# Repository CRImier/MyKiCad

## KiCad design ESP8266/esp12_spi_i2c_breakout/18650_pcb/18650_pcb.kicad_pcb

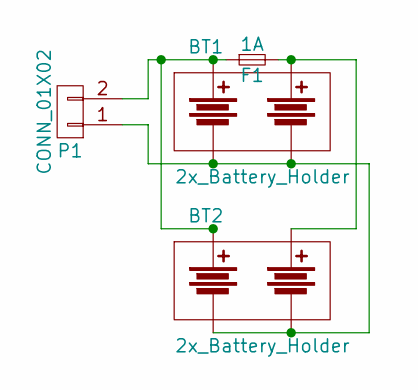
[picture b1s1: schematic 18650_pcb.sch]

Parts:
BT1: 2x_Battery_Holder; KEYSTONE_1048
BT2: 2x_Battery_Holder; BLM_18650_PC4
F1: 1A; Fuse_0679H
P1: CONN_01X02; TerminalBlock_Pheonix_PT-3.5mm_2pol

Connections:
unnamed: BT1.1, BT2.1, F1.1, P1.2
unnamed: BT1.2, BT2.2, F1.2
unnamed: BT1.3, BT1.4, BT2.3, BT2.4, P1.1

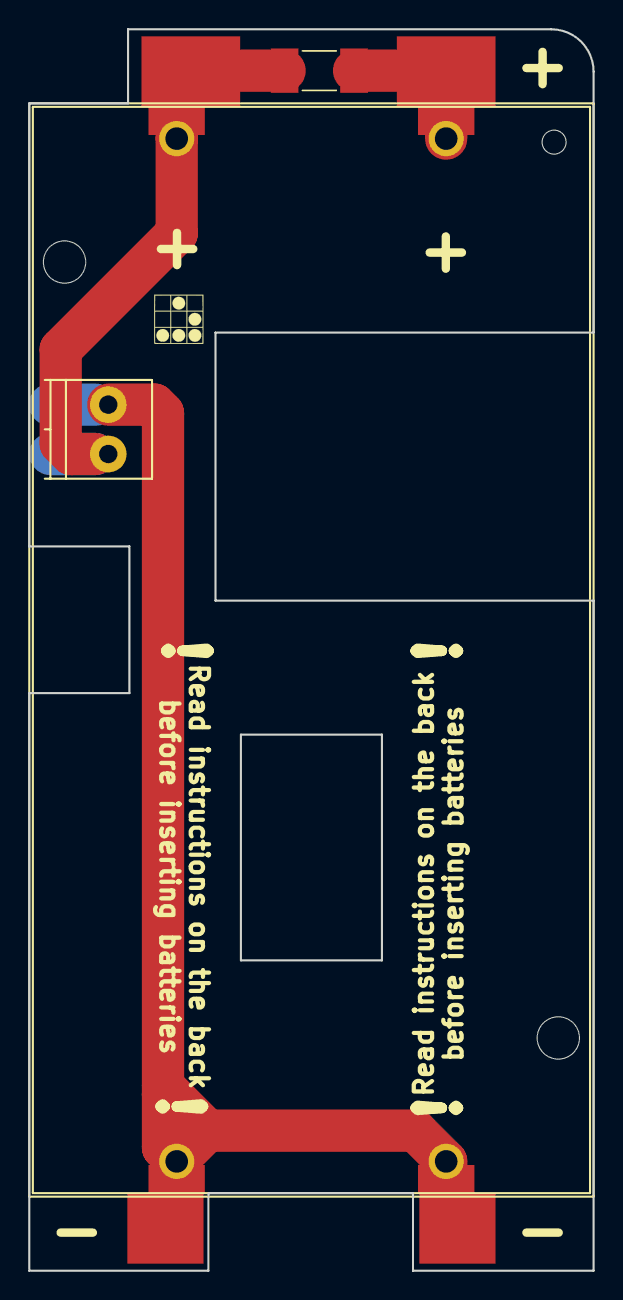
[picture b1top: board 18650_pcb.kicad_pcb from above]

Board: 2 copper layers, 40.0 x 88.0 mm, 4 parts (0 on the bottom side), 3 nets.

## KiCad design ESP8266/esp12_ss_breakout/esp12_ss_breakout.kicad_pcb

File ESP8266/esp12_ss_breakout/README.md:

# SaferSpace ESP12 entry panel controller

This is an entry panel ESP12 controller that can connect to the TTP229 board and the shift registers for LEDs,
as well as has I2C, UART and other connectors for extra devices that can be added.

This board has 5V and 3.3V linear regulators for the base components (ESP,595,TTP229) and also various devices
that could be connected in the future. It also has an RJ45 socket with a configurable pinout that's compatible
with regular passive PoE.

This board has THT cap footprints for regulators, but you can solder SMD caps on the TH pads instead.

Signal names are not silkscreened on the board, since I was ordering it in a rush.

- Version: 1
- PCB size: w*h
- Layer count: 2

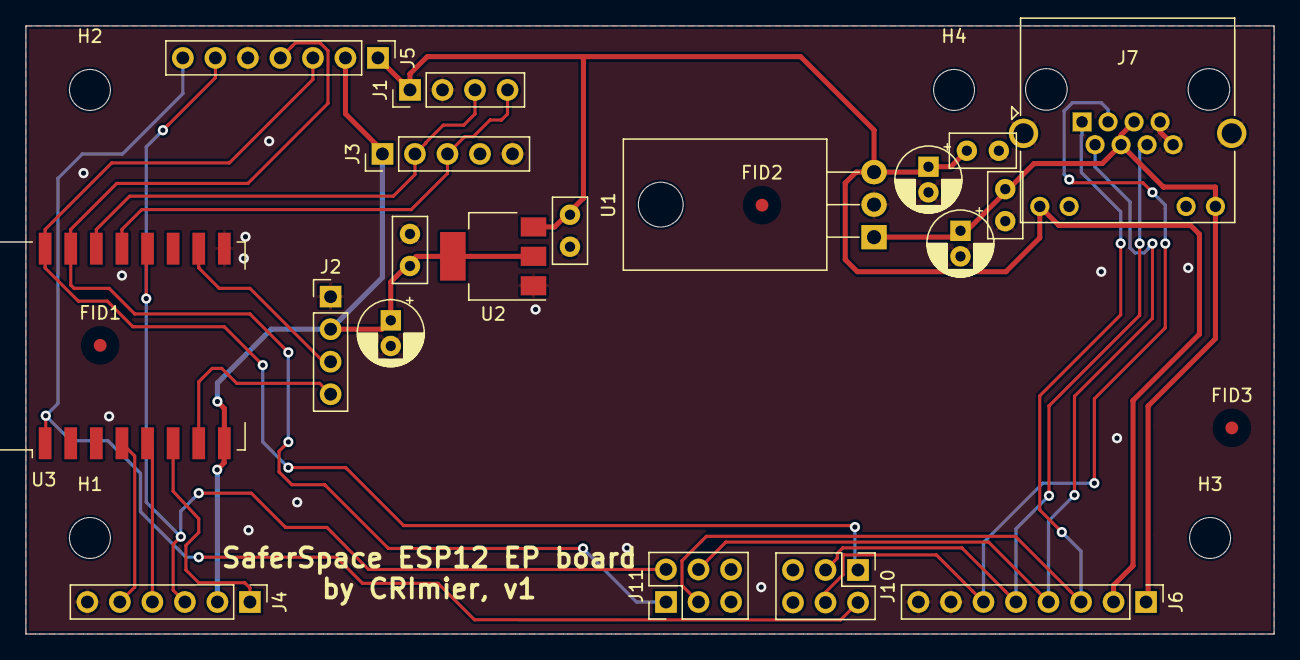
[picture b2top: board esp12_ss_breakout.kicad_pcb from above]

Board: 2 copper layers, 97.5 x 47.5 mm, 26 parts (0 on the bottom side), 19 nets.

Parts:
C4, C5, C6, C7: 100nF; C_Disc_D5.0mm_W2.5mm_P2.50mm
C10, C11, C12: 10uF; CP_Radial_D5.0mm_P2.00mm
FID1, FID2, FID3: Fiducial; Fiducial_1mm_Mask3mm
H1, H2, H3, H4: MountingHole; MountingHole_3.2mm_M3
J1: LCD; PinHeader_1x04_P2.54mm_Vertical
J2: KP; PinHeader_1x04_P2.54mm_Vertical
J3: I2C_RPI; PinHeader_1x05_P2.54mm_Vertical
J4: SHIFT; PinHeader_1x06_P2.54mm_Vertical
J5: PROG; PinHeader_1x07_P2.54mm_Vertical
J6: COMM; PinHeader_1x08_P2.54mm_Vertical
J7: COMM_RJ; RJ45_Amphenol_RJHSE538X
J10: 485_or_STR_TX; PinHeader_2x03_P2.54mm_Vertical
J11: 485_or_STR_RX; PinHeader_2x03_P2.54mm_Vertical
U1: L7805; TO-220-3_Horizontal_TabDown
U2: AP1117-33; SOT-223-3_TabPin2
U3: ESP-12E

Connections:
+3V3: C5.1, C12.1, J2.2, J3.1, J4.2, J5.2, U2.2, U3.8
+5V: C4.1, C7.1, C10.1, J1.1, J5.1, J6.2, J7.9, U1.3, U2.3
+VDC: C6.1, C11.1, J6.1, J7.4, J7.5, J7.12, U1.1
GND: C4.2, C5.2, C6.2, C7.2, C10.2, C11.2, C12.2, J1.2, J2.1, J3.5, J4.6, J5.5, J6.7, J6.8, J7.7, J7.8, J7.SH, U1.2, U2.1, U3.15
I2C_SCL: J1.4, J3.3, U3.19
I2C_SDA: J1.3, J3.2, U3.20
K_SCL: J2.4, U3.7
K_SDO: J2.3, U3.16
R1: J6.3, J7.1, J11.3
R2: J6.4, J7.2, J11.4
RST: J5.7, J10.2, U3.1
RX: J5.4, J11.1, U3.21
S_CLK: J4.4, U3.5
S_DAT: J4.3, J5.6, J11.2, U3.18
S_LAT: J4.5, U3.4
S_PWM: J4.1, U3.6
T1: J6.5, J7.6, J10.3
T2: J6.6, J7.3, J10.4
TX: J5.3, J10.1, U3.22

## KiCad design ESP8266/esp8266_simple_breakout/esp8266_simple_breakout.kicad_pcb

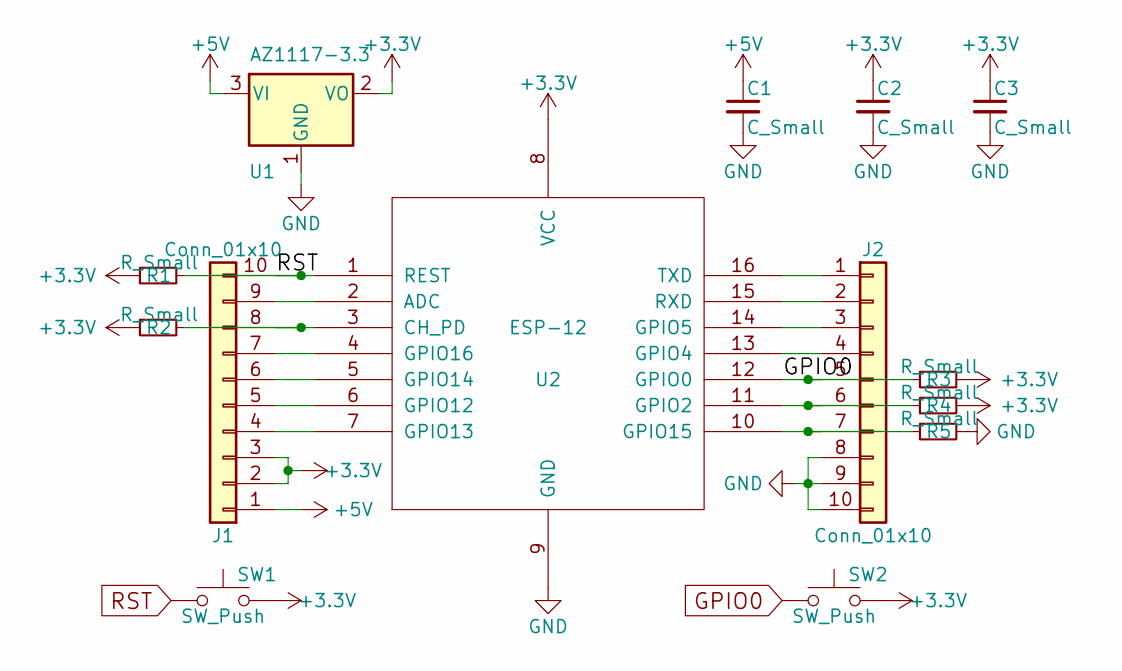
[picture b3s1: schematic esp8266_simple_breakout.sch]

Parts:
C1, C2, C3: C_Small; C_0805
J1, J2: Conn_01x10; Pin_Header_Straight_1x10_Pitch2.54mm
R1, R2, R3, R4, R5: R_Small; R_0603_HandSoldering
SW1, SW2: SW_Push; SW_SPST_EVQPE1
U1: AZ1117-3.3; SOT-223-3Lead_TabPin2
U2: ESP-12

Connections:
+3V3: C2.1, C3.1, J1.2, J1.3, R1.2, R2.2, R3.1, R4.1, SW1.2, SW2.2, U1.2 (VO), U2.8 (VCC)
+5V: C1.1, J1.1, U1.3 (VI)
GND: C1.2, C2.2, C3.2, J2.8, J2.9, J2.10, R5.1, U1.1 (GND), U2.9 (GND)
GPIO0: J2.5, R3.2, SW2.1, U2.12 (GPIO0)
unnamed: J1.4, U2.7 (GPIO13)
unnamed: J1.5, U2.6 (GPIO12)
unnamed: J1.6, U2.5 (GPIO14)
unnamed: J1.7, U2.4 (GPIO16)
unnamed: J1.8, R2.1, U2.3 (CH_PD)
unnamed: J1.9, U2.2 (ADC)
unnamed: J2.1, U2.16 (TXD)
unnamed: J2.2, U2.15 (RXD)
unnamed: J2.3, U2.14 (GPIO5)
unnamed: J2.4, U2.13 (GPIO4)
unnamed: J2.6, R4.2, U2.11 (GPIO2)
unnamed: J2.7, R5.2, U2.10 (GPIO15)
RST: J1.10, R1.1, SW1.1, U2.1 (REST)

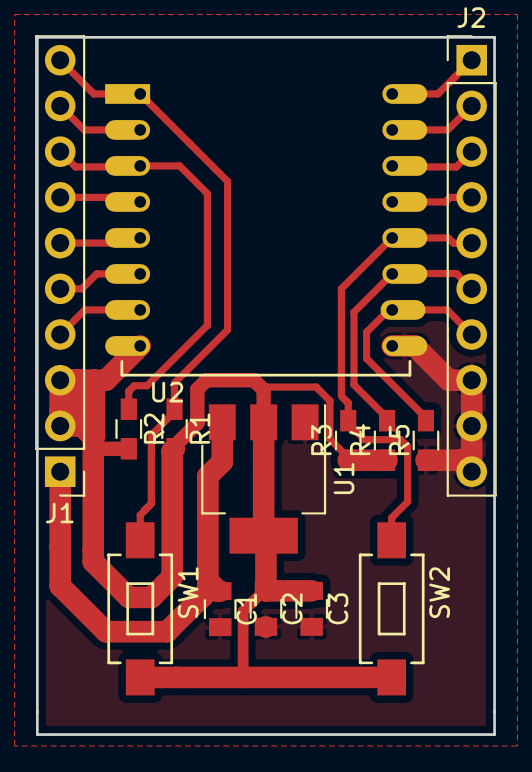
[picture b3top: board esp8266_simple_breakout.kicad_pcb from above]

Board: 2 copper layers, 25.4 x 38.7 mm, 14 parts (0 on the bottom side), 17 nets.

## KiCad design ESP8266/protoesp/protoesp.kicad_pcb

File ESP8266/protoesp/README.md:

# ProtoESP 8266

- [Main repo is here.](https://github.com/CRImier/ProtoESP/)
- [Project file releases are available here.](https://github.com/CRImier/ProtoESP/releases)
- [Board release thread on Twitter](https://twitter.com/CRImierTech/status/1481676889353773059)
- [Start of original Twitter thread chain, describing design intentions and process](https://twitter.com/CRImierTech/status/1473325419478847494)

Signal names are silkscreened on the board's bottom layers.

- Software: Kicad 7
- Version: ^__^
- PCB size: 97.5mmx90mm
- Layer count: 2

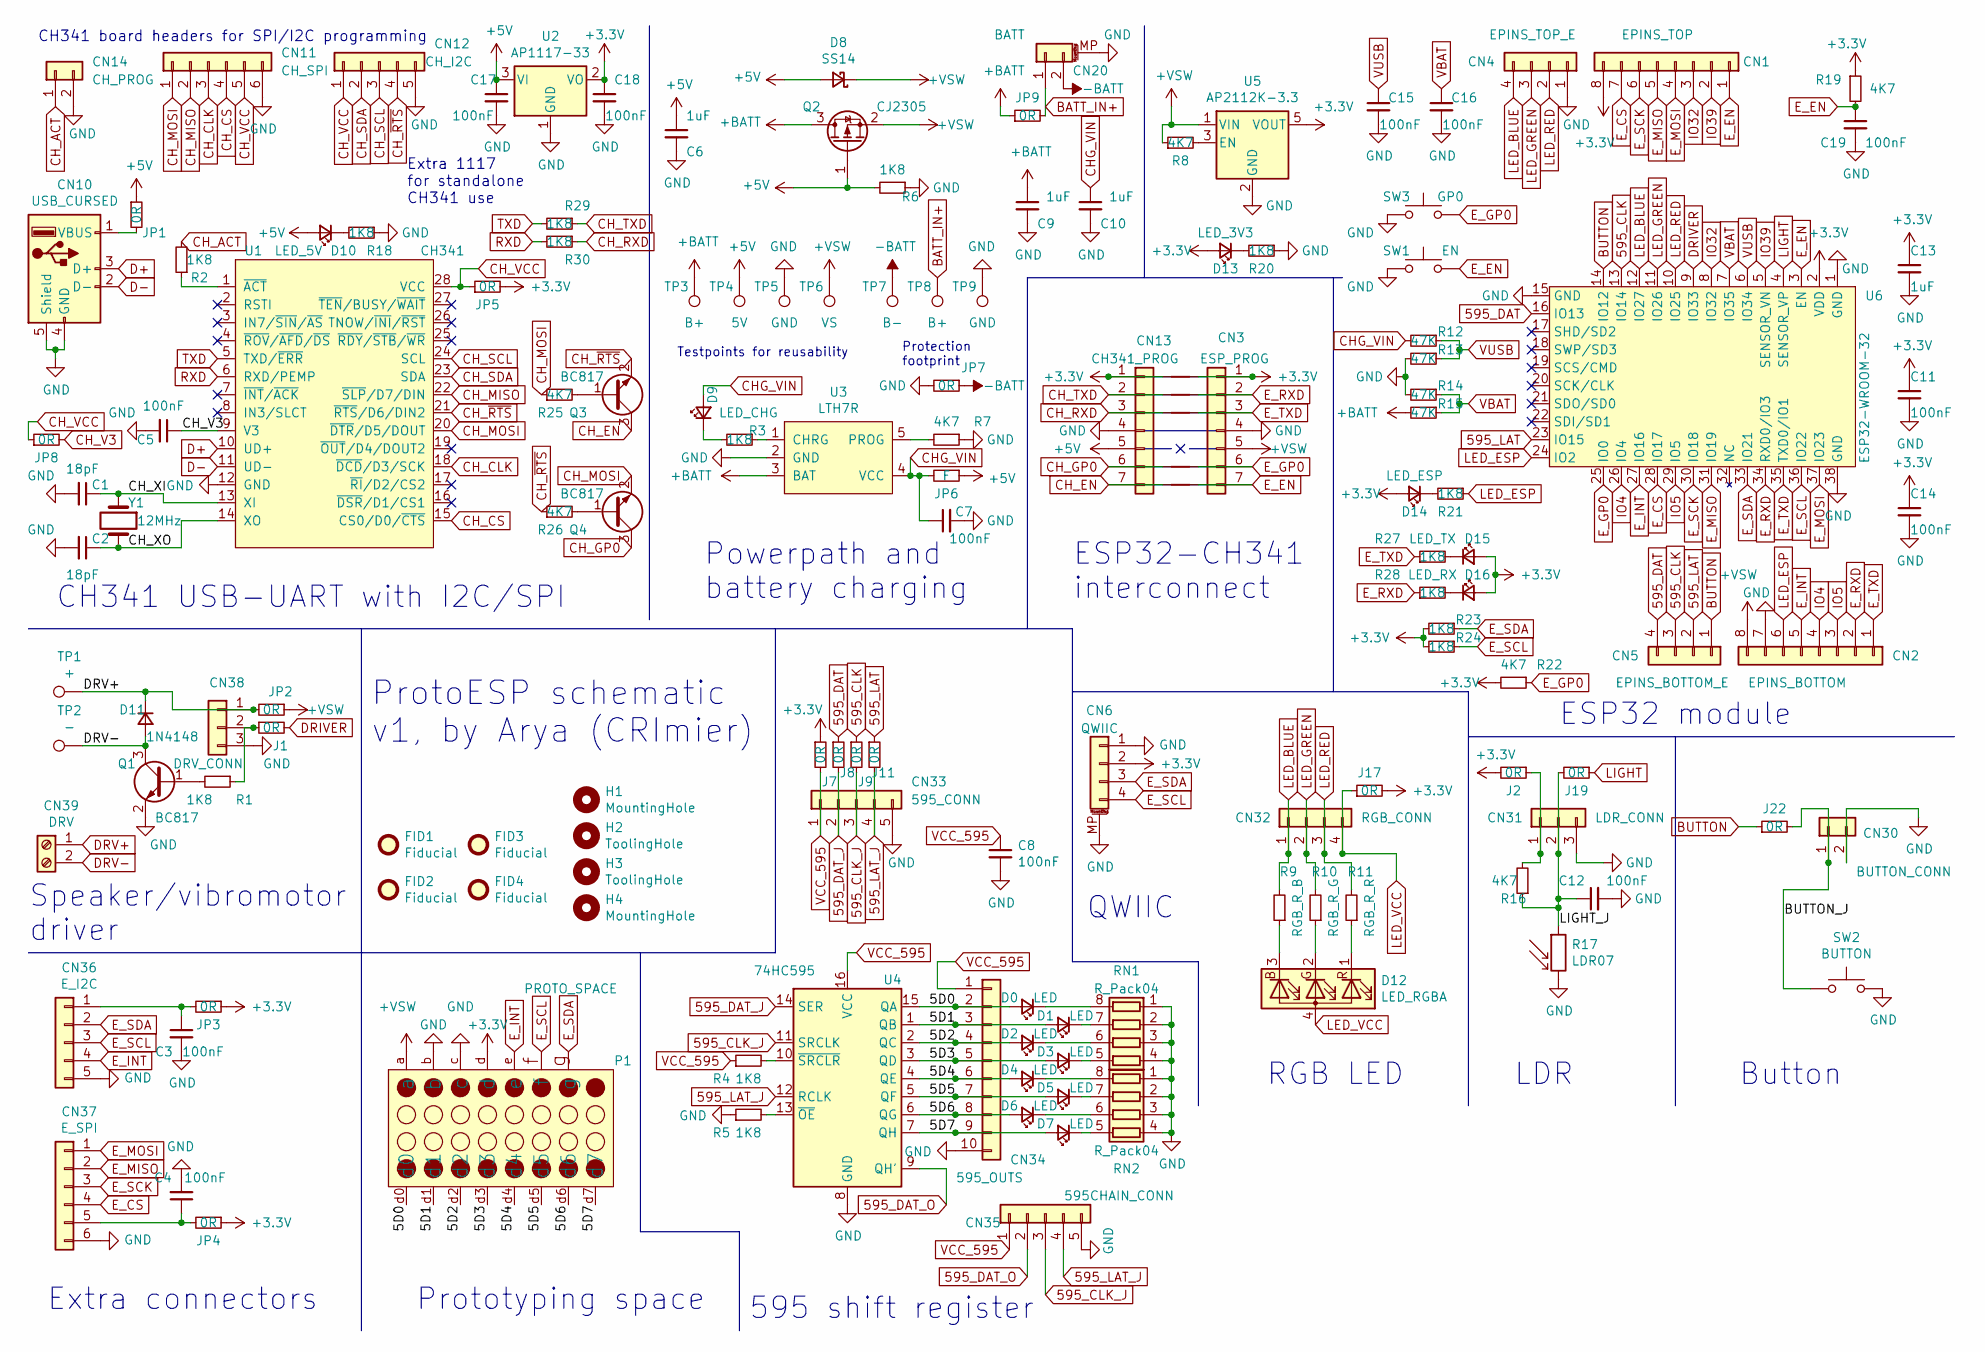
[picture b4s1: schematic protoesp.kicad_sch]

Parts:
C1, C2: 18pF; C_0603_1608Metric
C3, C4, C5, C7, C8, C11, C12, C14, C15, C16, C17, C18, C19: 100nF; C_0805_2012Metric
C6, C9, C10, C13: 1uF; C_0805_2012Metric
CN1: EPINS_TOP; PinHeader_1x08_P2.54mm_Vertical
CN2: EPINS_BOTTOM; PinHeader_1x08_P2.54mm_Vertical
CN3: ESP_PROG; PinHeader_1x07_P2.54mm_Vertical
CN4: EPINS_TOP_E; PinHeader_1x04_P2.54mm_Vertical
CN5: EPINS_BOTTOM_E; PinHeader_1x04_P2.54mm_Vertical
CN6: QWIIC; JST_SH_BM04B-SRSS-TB_1x04-1MP_P1.00mm_Vertical
CN10: USB_CURSED; USB_Combined
CN11: CH_SPI; PinSocket_1x06_P2.54mm_Horizontal
CN12: CH_I2C; PinSocket_1x05_P2.54mm_Horizontal
CN13: CH341_PROG; PinHeader_1x07_P2.54mm_Vertical
CN14: CH_PROG; PinSocket_1x02_P2.54mm_Vertical
CN20: BATT; JST_PH_S2B-PH-SM4-TB_02x2.00mm_Angled
CN30: BUTTON_CONN; PinHeader_1x02_P2.54mm_Vertical
CN31: LDR_CONN; PinHeader_1x03_P2.54mm_Vertical
CN32: RGB_CONN; PinHeader_1x04_P2.54mm_Vertical
CN33: 595_CONN; PinHeader_1x05_P2.54mm_Vertical
CN34: 595_OUTS; PinSocket_1x10_P2.54mm_Vertical
CN35: 595CHAIN_CONN; PinHeader_1x05_P2.54mm_Vertical
CN36: E_I2C; PinSocket_1x05_P2.54mm_Horizontal
CN37: E_SPI; PinSocket_1x06_P2.54mm_Horizontal
CN38: DRV_CONN; PinHeader_1x03_P2.54mm_Vertical
CN39: DRV; TerminalBlock_bornier-2_P5.08mm
D0, D1, D2, D3, D4, D5, D6, D7: LED; LED_0805_2012Metric
D8: SS14; D_SMA
D9: LED_CHG; LED_0805_2012Metric
D10: LED_5V; LED_0805_2012Metric
D11: 1N4148; D_SOD-123
D12: LED_RGBA; LED_RGB_1210
D13: LED_3V3; LED_0805_2012Metric
D14: LED_ESP; LED_0805_2012Metric
D15: LED_TX; LED_0805_2012Metric
D16: LED_RX; LED_0805_2012Metric
FID1, FID2, FID3, FID4: Fiducial; Fiducial_1mm_Mask2mm
H1, H4: MountingHole; JLCPCBToolingHole
H2, H3: ToolingHole; JLCPCBToolingHole
J1, J2, J7, J8, J9, J11, J17, J19, J22: 0R; R_0603_1608Metric
JP1, JP2, JP3, JP4, JP5, JP7, JP8, JP9: 0R; R_0805_2012Metric
JP6: F; R_0805_2012Metric
NT1, NT2, NT3, NT6, NT7: Net-Tie_2; NetTie-2_SMD_Pad0.5mm
P1: PROTO_SPACE; PROTO_THT_SMD_FULL
Q1, Q3, Q4: BC817; SOT-23
Q2: CJ2305; SOT-23
R1, R2, R3, R4, R5, R6, R18, R20, R21, R23, R24, R27, R28, R29, R30: 1K8; R_0603_1608Metric
R7, R8, R16, R19, R22, R25, R26: 4K7; R_0603_1608Metric
R9: RGB_R_B; R_0603_1608Metric
R10: RGB_R_G; R_0603_1608Metric
R11: RGB_R_R; R_0603_1608Metric
R12, R13, R14, R15: 47K; R_0603_1608Metric
R17: LDR07; R_LDR_5.1x4.3mm_P3.4mm_Vertical
RN1, RN2: R_Pack04; R_Array_Concave_4x0603
SW1: EN; SW_SPST_SKQG_WithStem
SW2: BUTTON; SW_SPST_SKQG_WithStem
SW3: GP0; SW_SPST_SKQG_WithStem
TP1: +; TestPoint_Pad_2.0x2.0mm
TP2: -; TestPoint_Pad_2.0x2.0mm
TP3, TP8: B+; TestPoint_Pad_2.0x2.0mm
TP4: 5V; TestPoint_Pad_2.0x2.0mm
TP5, TP9: GND; TestPoint_Pad_2.0x2.0mm
TP6: VS; TestPoint_Pad_2.0x2.0mm
TP7: B-; TestPoint_Pad_2.0x2.0mm
U1: CH341; SOIC-28W_SOIC16_CH34x_Combined
U2: AP1117-33; SOT-223-3_TabPin2
U3: LTH7R; SOT-23-5
U4: 74HC595; SOP-16_4.55x10.3mm_P1.27mm
U5: AP2112K-3.3; SOT-23-5
U6: ESP32-WROOM-32
Y1: 12MHz; Crystal_HC49-U_Vertical

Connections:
595_CLK: CN5.3, J9.1, U6.13 (IO14)
595_CLK_J: CN33.3, CN35.3, J9.2, U4.11 (SRCLK)
595_DAT: CN5.4, J8.1, U6.16 (IO13)
595_DAT_J: CN33.2, J8.2, U4.14 (SER)
595_DAT_O: CN35.2, U4.9 (QH')
595_LAT: CN5.2, J11.1, U6.23 (IO15)
595_LAT_J: CN33.4, CN35.4, J11.2, U4.12 (RCLK)
+3V3: C11.1, C13.1, C14.1, C18.1, CN1.8, CN3.1, CN6.2, CN13.1, D13.2 (A), D14.2 (A), D15.2 (A), D16.2 (A), J2.2, J7.1, J17.2, JP3.1, JP4.1, JP5.2, NT1.1, NT1.2, P1.d, R19.1, R22.2, R23.2, R24.2, U2.2 (VO), U5.5 (VOUT), U6.2 (VDD)
+5V: C6.1, C17.1, CN13.5, D8.2 (A), D10.2 (A), JP1.1, JP6.1, Q2.1 (G), R6.2, TP4.1, U2.3 (VI)
+BATT: C9.1, JP9.1, Q2.3 (D), R15.2, TP3.1, U3.3 (BAT)
+VSW: CN2.8, CN3.5, D8.1 (K), JP2.1, P1.a, Q2.2 (S), R8.1, TP6.1, U5.1 (VIN)
-BATT: CN20.2, JP7.1, TP7.1
/5D0: CN34.2, D0.2 (A), P1.d0, U4.15 (QA)
/5D1: CN34.3, D1.2 (A), P1.d1, U4.1 (QB)
/5D2: CN34.4, D2.2 (A), P1.d2, U4.2 (QC)
/5D3: CN34.5, D3.2 (A), P1.d3, U4.3 (QD)
/5D4: CN34.6, D4.2 (A), P1.d4, U4.4 (QE)
/5D5: CN34.7, D5.2 (A), P1.d5, U4.5 (QF)
/5D6: CN34.8, D6.2 (A), P1.d6, U4.6 (QG)
/5D7: CN34.9, D7.2 (A), P1.d7, U4.7 (QH)
/BUTTON_J: CN30.1, J22.2, SW2.1
/CH_XI: C1.1, U1.13 (XI), Y1.1
/CH_XO: C2.1, U1.14 (XO), Y1.2
/LIGHT_J: C12.1, CN31.2, J19.2, R16.1, R17.1
BATT_IN+: CN20.1, JP9.2, TP8.1
BUTTON: CN5.1, J22.1, U6.14 (IO12)
CHG_VIN: C7.1, C10.1, D9.2 (A), JP6.2, R12.2, U3.4 (VCC)
CH_ACT: CN14.1, R2.2
CH_CLK: CN11.3, U1.18 (~DCD/D3/SCK)
CH_CS: CN11.4, U1.15 (CS0/D0/~CTS)
CH_EN: CN13.7, NT7.1, Q3.3 (C)
CH_GP0: CN13.6, NT6.1, Q4.3 (C)
CH_MISO: CN11.2, U1.22 (~SLP/D7/DIN)
CH_MOSI: CN11.1, Q4.2 (E), R25.1, U1.20 (~DTR/D5/DOUT)
CH_RXD: CN13.3, NT3.1, R30.1
CH_SCL: CN12.3, U1.24 (SCL)
CH_SDA: CN12.2, U1.23 (SDA)
CH_TXD: CN13.2, NT2.1, R29.1
CH_V3: C5.1, JP8.2, U1.9 (V3)
CH_VCC: CN11.5, CN12.1, JP5.1, JP8.1, U1.28 (VCC)
CH_~RTS: CN12.4, Q3.2 (E), R26.1, U1.21 (~RTS/D6/DIN2)
D+: CN10.3 (D+), U1.10 (UD+)
D-: CN10.2 (D-), U1.11 (UD-)
DRIVER: J1.2, U6.9 (IO33)
DRV+: CN38.1, CN39.1, D11.1 (K), JP2.2, TP1.1
DRV-: CN39.2, D11.2 (A), Q1.3 (C), TP2.1
E_CS: CN1.7, CN37.4, U6.28 (IO17)
E_EN: C19.1, CN1.1, CN3.7, NT7.2, R19.2, SW1.2, U6.3 (EN)
E_GP0: CN3.6, NT6.2, R22.1, SW3.2, U6.25 (IO0)
E_INT: CN2.5, CN36.4, P1.e, U6.27 (IO16)
E_MISO: CN1.5, CN37.2, U6.31 (IO19)
E_MOSI: CN1.4, CN37.1, U6.37 (IO23)
E_RXD: CN2.2, CN3.2, NT2.2, R28.1, U6.34 (RXD0/IO3)
E_SCK: CN1.6, CN37.3, U6.30 (IO18)
E_SCL: CN6.4, CN36.3, P1.f, R24.1, U6.36 (IO22)
E_SDA: CN6.3, CN36.2, P1.g, R23.1, U6.33 (IO21)
E_TXD: CN2.1, CN3.3, NT3.2, R27.1, U6.35 (TXD0/IO1)
GND: C1.2, C2.2, C3.2, C4.2, C5.2, C6.2, C7.2, C8.2, C9.2, C10.2, C11.2, C12.2, C13.2, C14.2, C15.2, C16.2, C17.2, C18.2, C19.2, CN2.7, CN3.4, CN4.1, CN6.1, CN6.MP (MountPin), CN10.4 (GND), CN10.5 (Shield), CN11.6, CN12.5, CN13.4, CN14.2, CN20.MP (MountPin), CN30.2, CN31.3, CN33.5, CN34.10, CN35.5, CN36.5, CN37.6, CN38.3, JP7.2, P1.b, P1.c, Q1.2 (E), R5.1, R6.1, R7.1, R13.2, R14.2, R17.2, R18.1, R20.1, RN1.1 (R1.1), RN1.2 (R2.1), RN1.3 (R3.1), RN1.4 (R4.1), RN2.1 (R1.1), RN2.2 (R2.1), RN2.3 (R3.1), RN2.4 (R4.1), SW1.1, SW2.2, SW3.1, TP5.1, TP9.1, U1.12 (GND), U2.1 (GND), U3.2 (GND), U4.8 (GND), U5.2 (GND), U6.1 (GND), U6.15 (GND), U6.38 (GND), U6.39 (GND)
IO4: CN2.4, U6.26 (IO4)
IO5: CN2.3, U6.29 (IO5)
IO32: CN1.3, U6.8 (IO32)
IO39: CN1.2, U6.5 (SENSOR_VN)
LED_BLUE: CN4.4, CN32.1, R9.2, U6.12 (IO27)
LED_ESP: CN2.6, R21.1, U6.24 (IO2)
LED_GREEN: CN4.3, CN32.2, R10.2, U6.11 (IO26)
LED_RED: CN4.2, CN32.3, R11.2, U6.10 (IO25)
LED_VCC: CN32.4, D12.4 (A), J17.1
LIGHT: J19.1, U6.4 (SENSOR_VP)
unnamed: C3.1, CN36.1, JP3.2
unnamed: C4.1, CN37.5, JP4.2
unnamed: CN10.1 (VBUS), JP1.2
unnamed: CN31.1, J2.1, R16.2
unnamed: CN38.2, J1.1, R1.1
unnamed: D0.1 (K), RN1.8 (R1.2)
unnamed: D1.1 (K), RN1.7 (R2.2)
unnamed: D2.1 (K), RN1.6 (R3.2)
unnamed: D3.1 (K), RN1.5 (R4.2)
unnamed: D4.1 (K), RN2.8 (R1.2)
unnamed: D5.1 (K), RN2.7 (R2.2)
unnamed: D6.1 (K), RN2.6 (R3.2)
unnamed: D7.1 (K), RN2.5 (R4.2)
unnamed: D9.1 (K), R3.2
unnamed: D10.1 (K), R18.2
unnamed: D12.1 (RK), R11.1
unnamed: D12.2 (GK), R10.1
unnamed: D12.3 (BK), R9.1
unnamed: D13.1 (K), R20.2
unnamed: D14.1 (K), R21.2
unnamed: D15.1 (K), R27.2
unnamed: D16.1 (K), R28.2
unnamed: Q1.1 (B), R1.2
unnamed: Q3.1 (B), R25.2
unnamed: Q4.1 (B), R26.2
unnamed: R2.1, U1.1 (~ACT)
unnamed: R3.1, U3.1 (CHRG)
unnamed: R4.2, U4.10 (~SRCLR)
unnamed: R5.2, U4.13 (~OE)
unnamed: R7.2, U3.5 (PROG)
unnamed: R8.2, U5.3 (EN)
RXD: R30.2, U1.6 (RXD/PEMP)
TXD: R29.2, U1.5 (TXD/~ERR)
VBAT: C16.1, R14.1, R15.1, U6.7 (IO35)
VCC_595: C8.1, CN33.1, CN34.1, CN35.1, J7.2, R4.1, U4.16 (VCC)
VUSB: C15.1, R12.1, R13.1, U6.6 (IO34)

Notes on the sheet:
Extra connectors
Protection footprint
Prototyping space
ESP32-CH341 interconnect
ProtoESP schematic v1, by Arya (CRImier)
Testpoints for reusability
CH341 USB-UART with I2C/SPI
Powerpath and battery charging
ESP32 module
595 shift register
Button
Extra 1117 for standalone CH341 use
CH341 board headers for SPI/I2C programming
RGB LED
LDR
QWIIC
Speaker/vibromotor driver

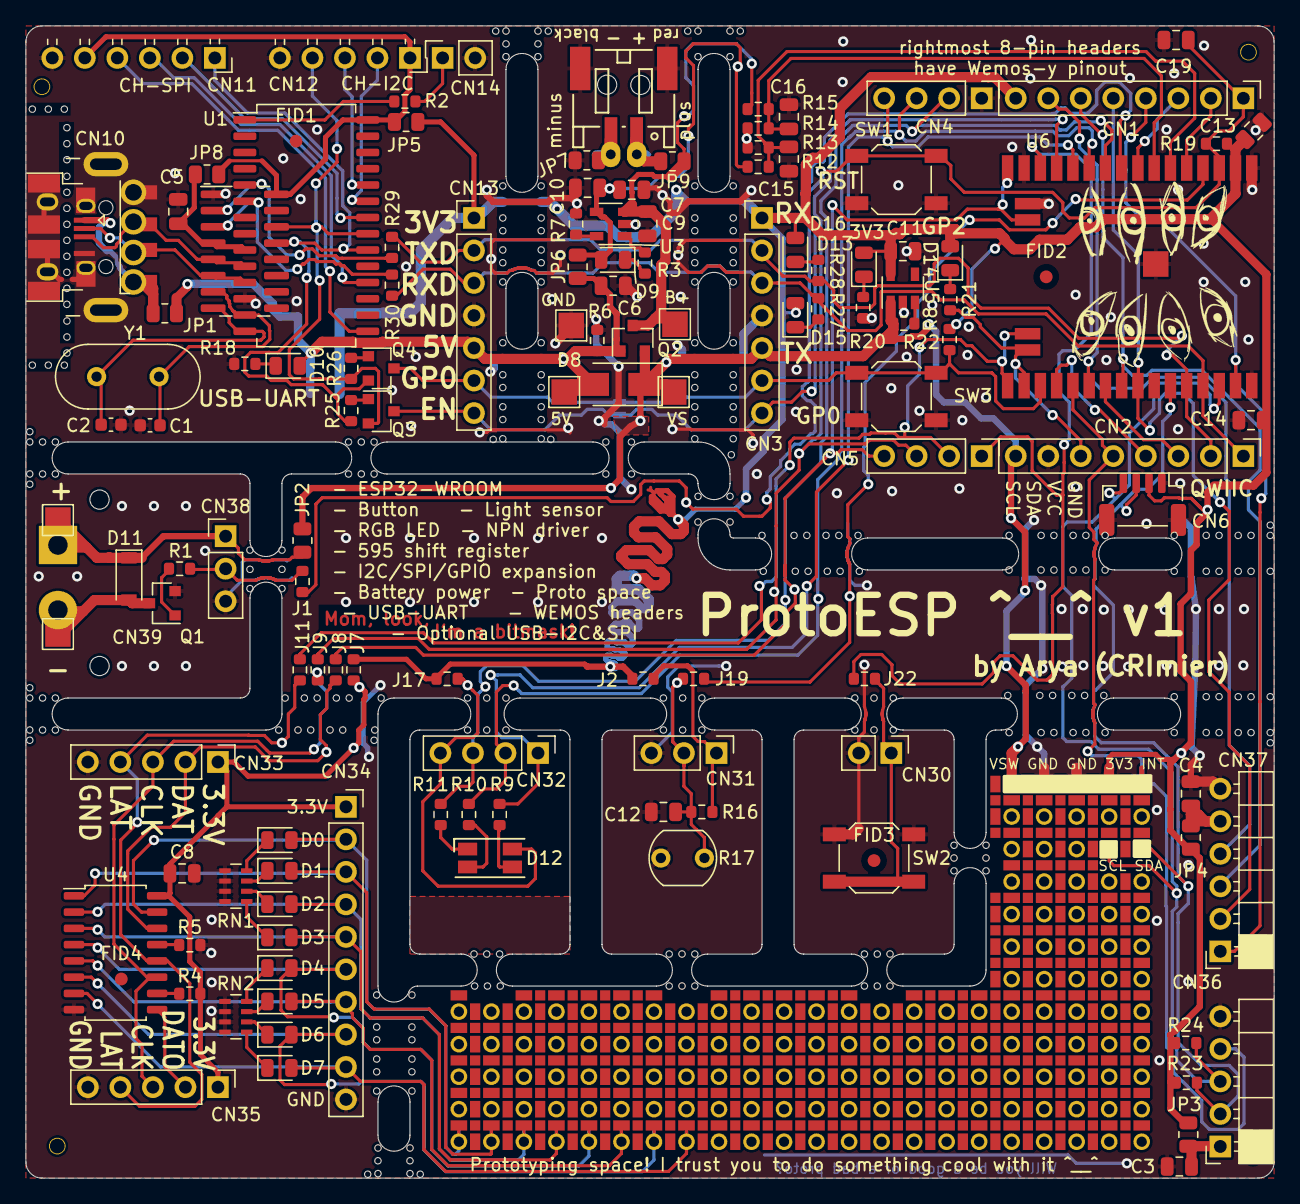
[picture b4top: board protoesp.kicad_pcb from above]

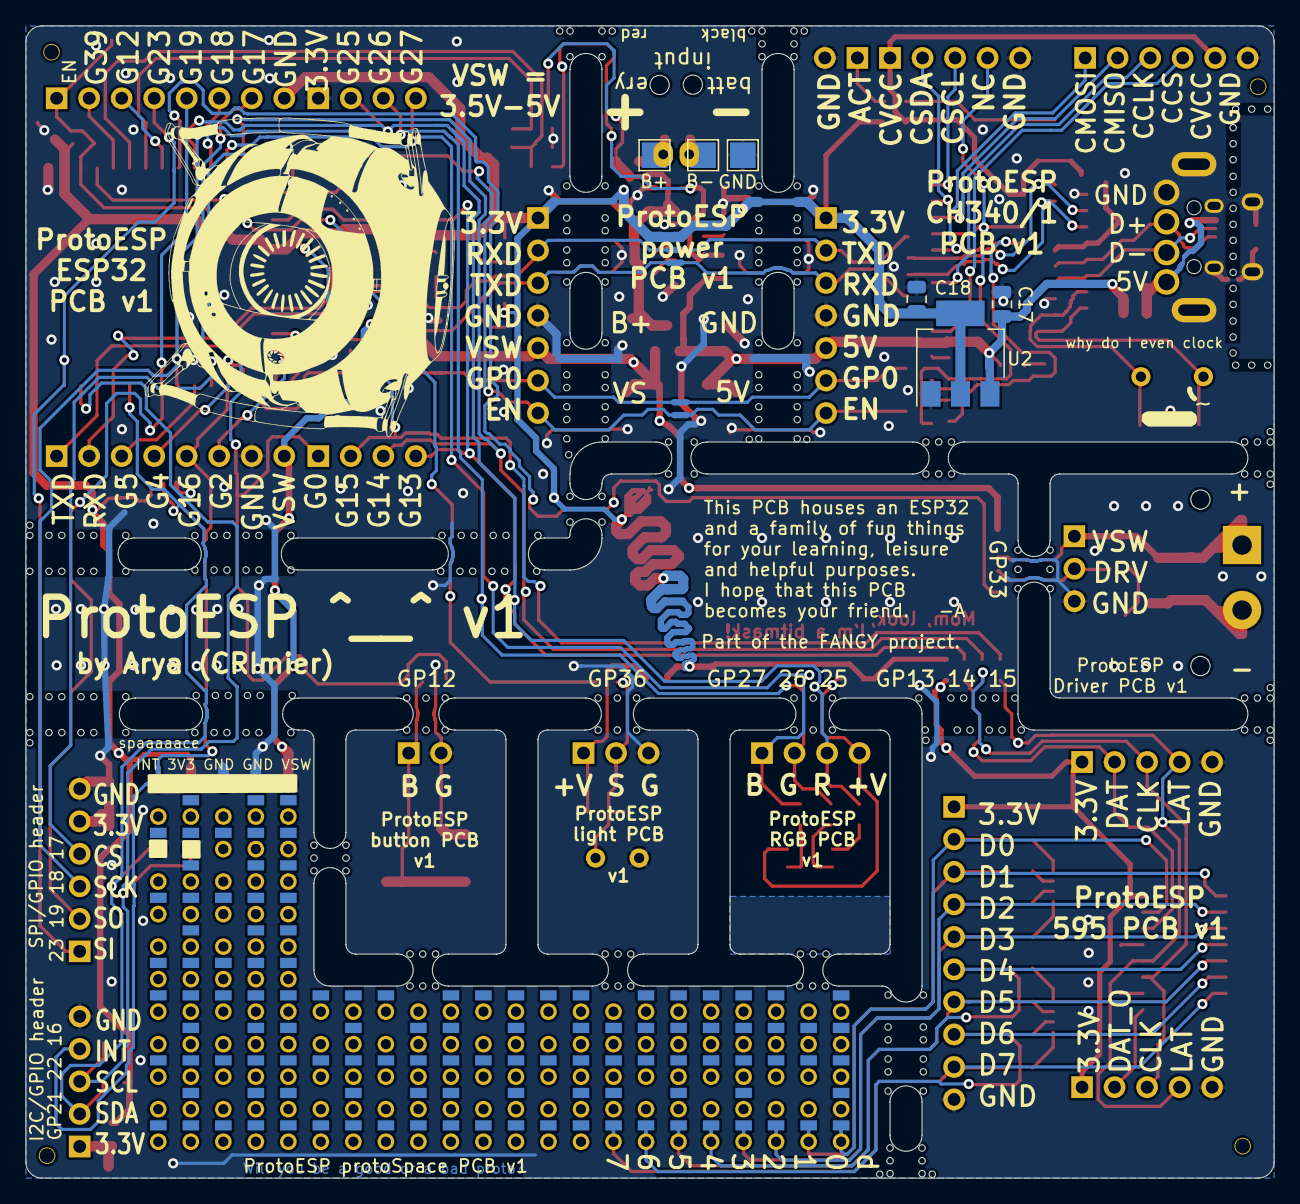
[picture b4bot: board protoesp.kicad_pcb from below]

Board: 2 copper layers, 97.5 x 90.0 mm, 149 parts (11 on the bottom side), 104 nets.

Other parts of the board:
H1#2, H1#3, H1#5: pin_hole; PinHole_1,5mm
H1#4: MountingHole; JLCPCBToolingHole

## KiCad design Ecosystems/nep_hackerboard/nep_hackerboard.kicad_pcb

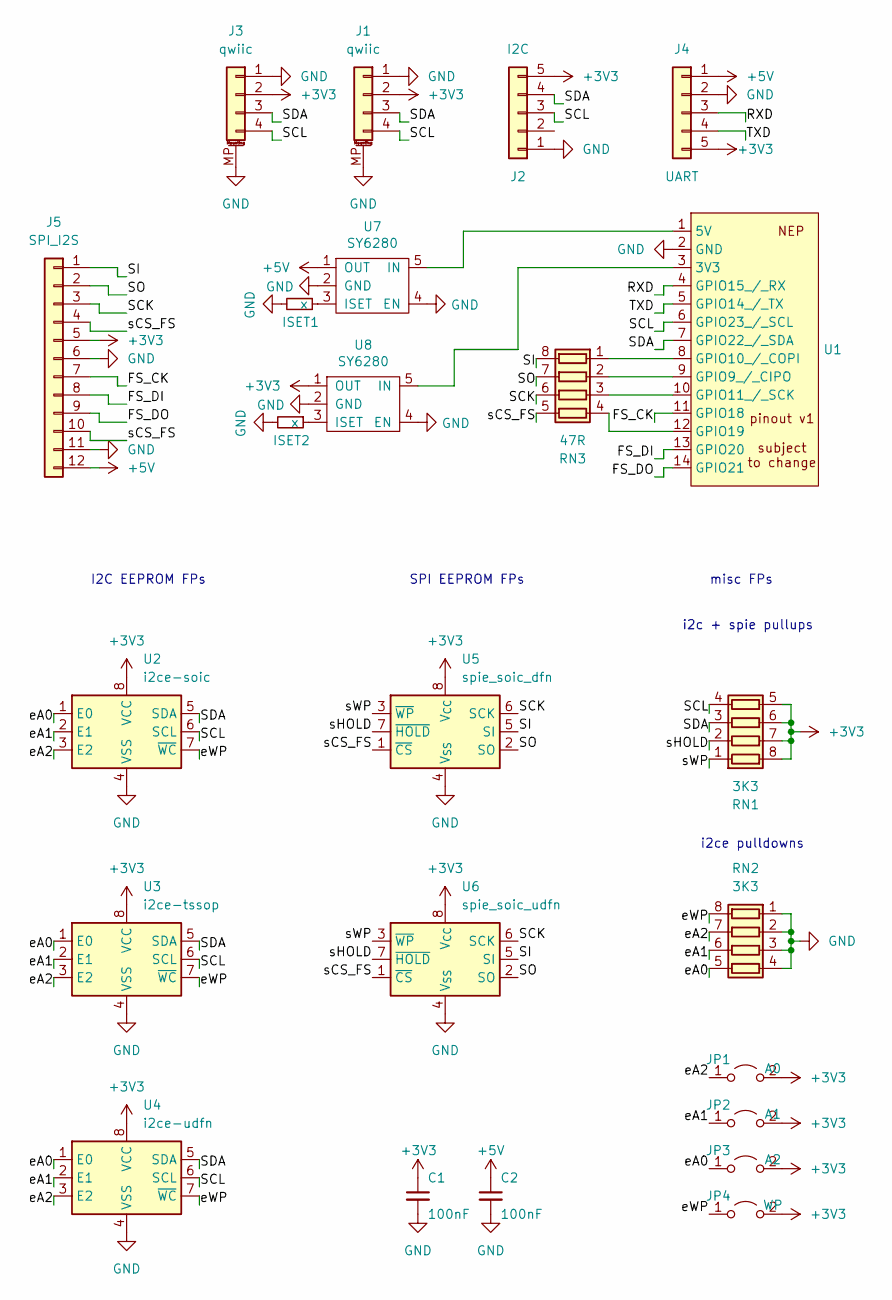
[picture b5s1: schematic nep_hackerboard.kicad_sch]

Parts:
C1, C2: 100nF; C_0603_1608Metric
ISET1, ISET2: x; R_0603_1608Metric
J1, J3: qwiic; JST_SH_SM04B-SRSS-TB_1x04-1MP_P1.00mm_Horizontal
J2: I2C; PinHeader_1x05_P2.54mm_Vertical
J4: UART; PinHeader_1x05_P2.54mm_Vertical
J5: SPI_I2S; PinHeader_1x12_P2.54mm_Vertical
JP1: A0; SolderJumper-2_P1.3mm_Open_Pad1.0x1.5mm
JP2: A1; SolderJumper-2_P1.3mm_Open_Pad1.0x1.5mm
JP3: A2; SolderJumper-2_P1.3mm_Open_Pad1.0x1.5mm
JP4: WP; SolderJumper-2_P1.3mm_Open_Pad1.0x1.5mm
RN1, RN2: 3K3; R_Array_Convex_4x0603
RN3: 47R; R_Array_Convex_4x0603
U1: PinHeader_1x14_P2.54mm_Vertical
U2: i2ce-soic; SOIC-8_3.9x4.9mm_P1.27mm
U3: i2ce-tssop; TSSOP-8_4.4x3mm_P0.65mm
U4: i2ce-udfn; DFN-8-1EP_3x2mm_P0.5mm_EP1.3x1.5mm
U5: spie_soic_dfn; SOIC-8W_5.3x5.3mm_P1.27mm
U6: spie_soic_udfn; DFN-8-1EP_3x2mm_P0.5mm_EP1.3x1.5mm
U7, U8: SY6280; SOT-23-5

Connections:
+3V3: C1.1, J1.2, J2.5, J3.2, J4.5, J5.5, JP1.2 (B), JP2.2 (B), JP3.2 (B), JP4.2 (B), RN1.5 (R4.2), RN1.6 (R3.2), RN1.7 (R2.2), RN1.8 (R1.2), U2.8 (VCC), U3.8 (VCC), U4.8 (VCC), U5.8 (V_{CC}), U6.8 (V_{CC}), U8.1 (OUT)
+5V: C2.1, J4.1, J5.12, U7.1 (OUT)
/FS_CK: J5.7, U1.11 (GPIO18)
/FS_DI: J5.8, U1.13 (GPIO20)
/FS_DO: J5.9, U1.14 (GPIO21)
/RXD: J4.3, U1.4 (GPIO15_/_RX)
/SCK: J5.3, RN3.6 (R3.2), U5.6 (SCK), U6.6 (SCK)
/SCL: J1.4, J2.3, J3.4, RN1.4 (R4.1), U1.6 (GPIO23_/_SCL), U2.6 (SCL), U3.6 (SCL), U4.6 (SCL)
/SDA: J1.3, J2.4, J3.3, RN1.3 (R3.1), U1.7 (GPIO22_/_SDA), U2.5 (SDA), U3.5 (SDA), U4.5 (SDA)
/SI: J5.1, RN3.8 (R1.2), U5.5 (SI), U6.5 (SI)
/SO: J5.2, RN3.7 (R2.2), U5.2 (SO), U6.2 (SO)
/TXD: J4.4, U1.5 (GPIO14_/_TX)
/eA0: JP3.1 (A), RN2.5 (R4.2), U2.1 (E0), U3.1 (E0), U4.1 (E0)
/eA1: JP2.1 (A), RN2.6 (R3.2), U2.2 (E1), U3.2 (E1), U4.2 (E1)
/eA2: JP1.1 (A), RN2.7 (R2.2), U2.3 (E2), U3.3 (E2), U4.3 (E2)
/eWP: JP4.1 (A), RN2.8 (R1.2), U2.7 (~WC), U3.7 (~WC), U4.7 (~WC)
/sCS_FS: J5.4, J5.10, RN3.5 (R4.2), U5.1 (~CS), U6.1 (~CS)
/sHOLD: RN1.2 (R2.1), U5.7 (~HOLD), U6.7 (~HOLD)
/sWP: RN1.1 (R1.1), U5.3 (~WP), U6.3 (~WP)
GND: C1.2, C2.2, ISET1.2, ISET2.2, J1.1, J1.MP (MountPin), J2.1, J3.1, J3.MP (MountPin), J4.2, J5.6, J5.11, RN2.1 (R1.1), RN2.2 (R2.1), RN2.3 (R3.1), RN2.4 (R4.1), U1.2 (GND), U2.4 (VSS), U3.4 (VSS), U4.4 (VSS), U5.4 (V_{SS}), U6.4 (V_{SS}), U7.2 (GND), U7.4 (EN), U8.2 (GND), U8.4 (EN)
unnamed: RN3.1 (R1.1), U1.8 (GPIO10_/_COPI)
unnamed: RN3.2 (R2.1), U1.9 (GPIO9_/_CIPO)
unnamed: RN3.3 (R3.1), U1.10 (GPIO11_/_SCK)
unnamed: RN3.4 (R4.1), U1.12 (GPIO19)
unnamed: U1.3 (3V3), U8.5 (IN)
unnamed: U1.1 (5V), U7.5 (IN)
unnamed: ISET1.1, U7.3 (ISET)
unnamed: ISET2.1, U8.3 (ISET)

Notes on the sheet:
I2C EEPROM FPs
SPI EEPROM FPs
misc FPs
i2ce pulldowns
i2c + spie pullups

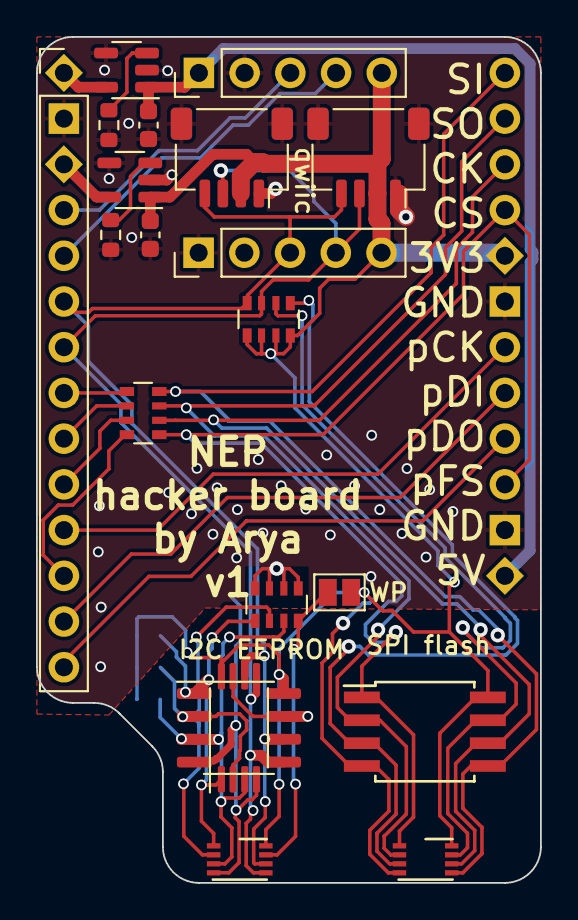
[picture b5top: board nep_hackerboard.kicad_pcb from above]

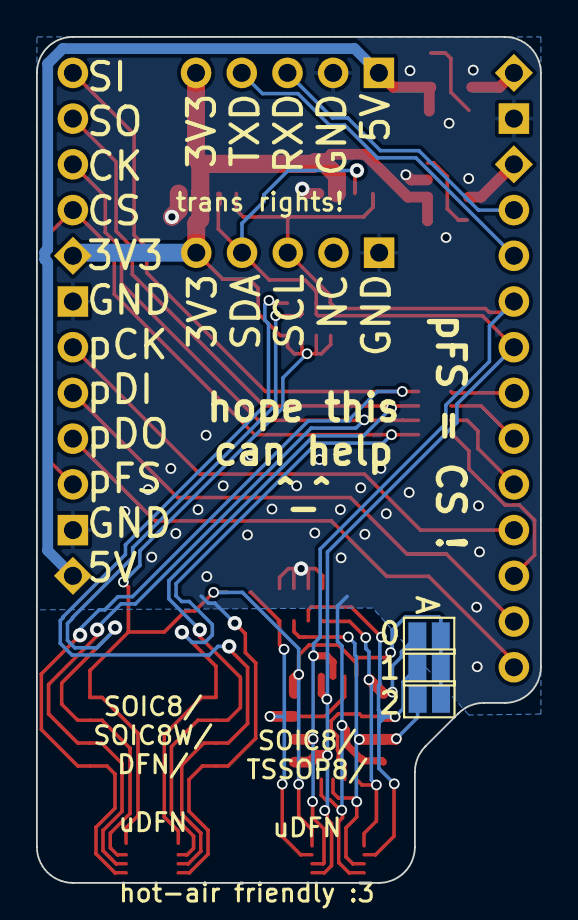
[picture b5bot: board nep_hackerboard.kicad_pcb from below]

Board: 2 copper layers, 28.0 x 47.0 mm, 24 parts (3 on the bottom side), 28 nets.
